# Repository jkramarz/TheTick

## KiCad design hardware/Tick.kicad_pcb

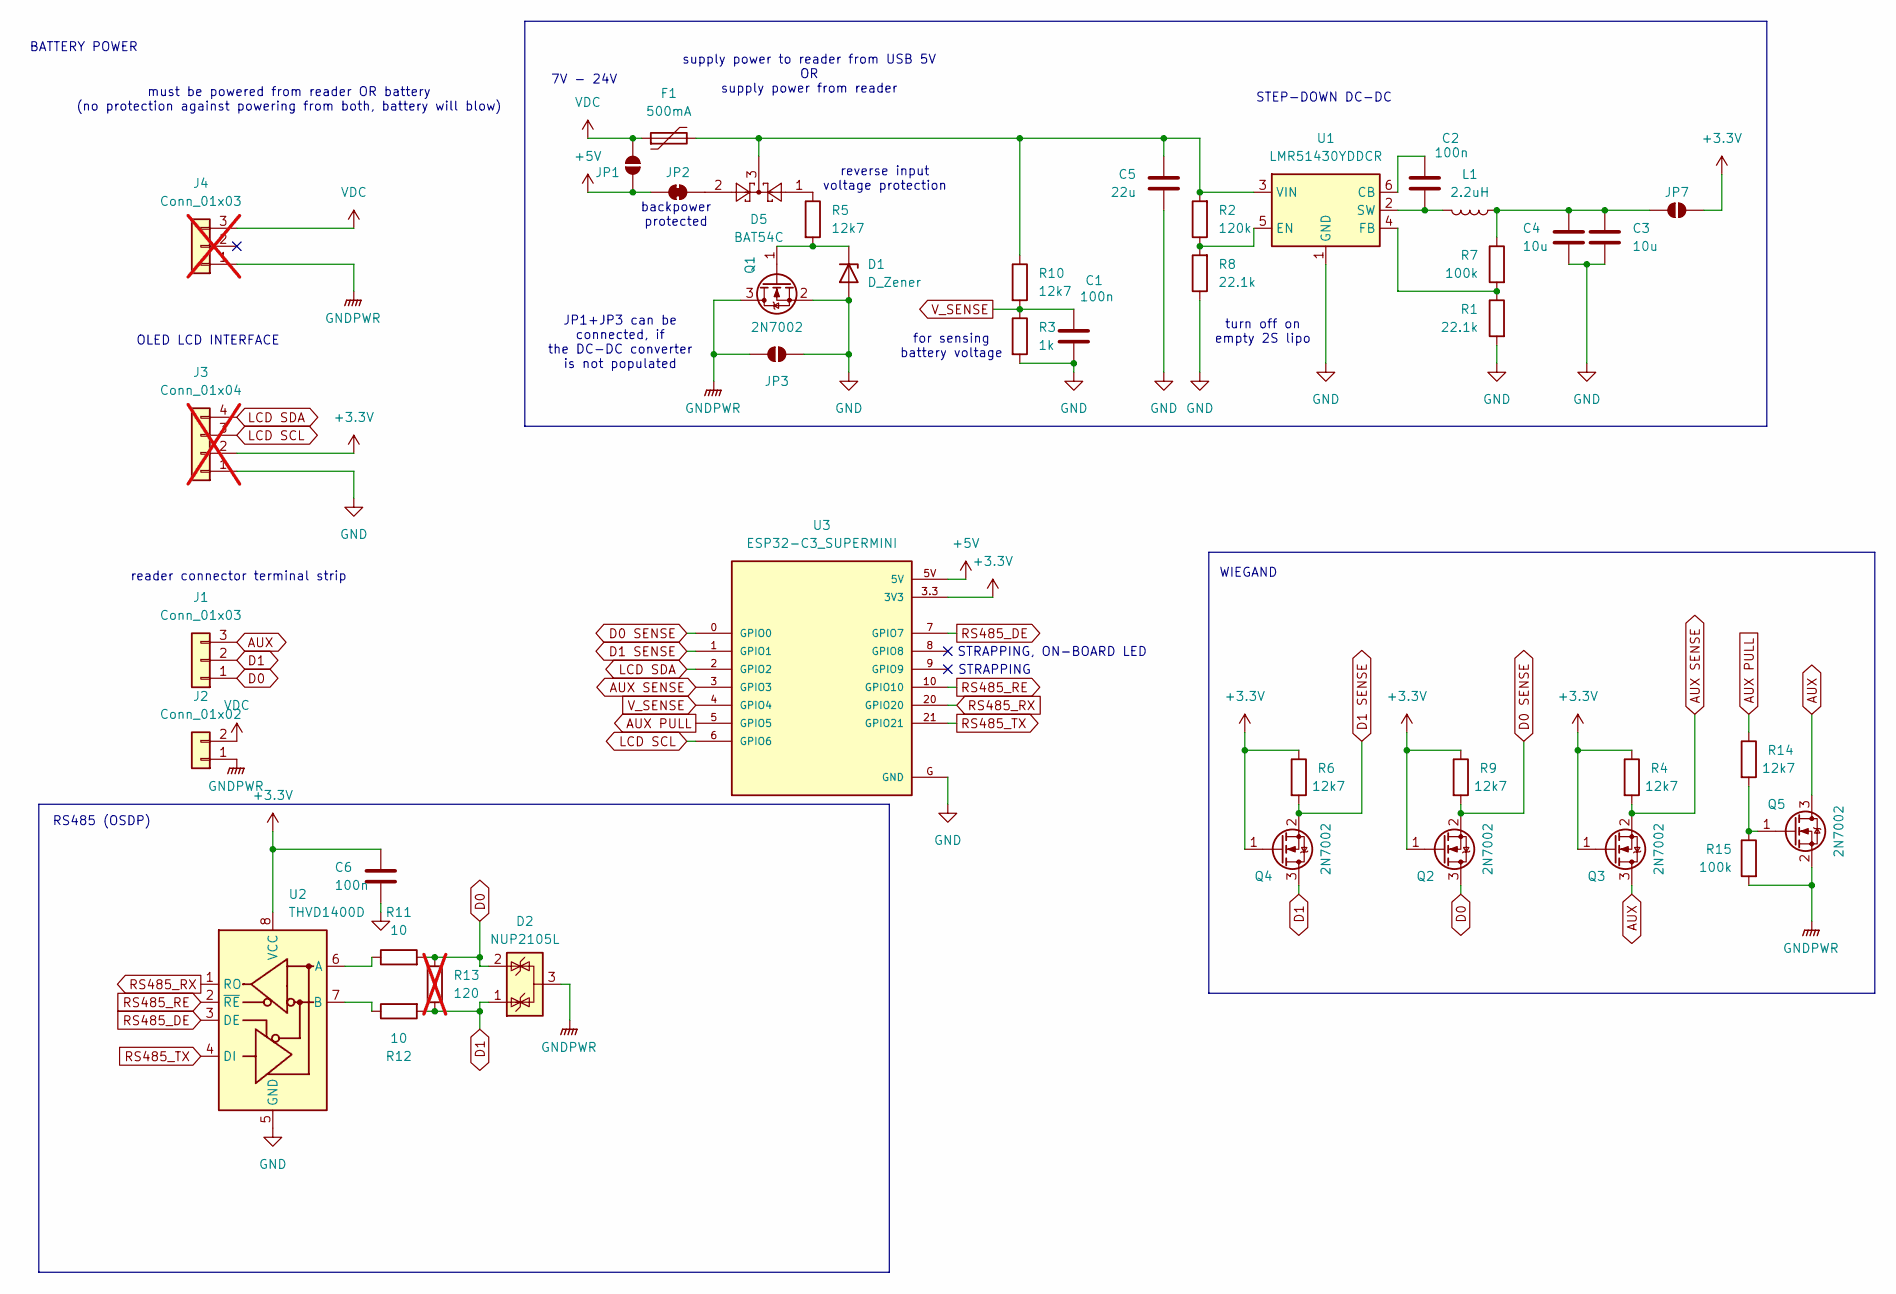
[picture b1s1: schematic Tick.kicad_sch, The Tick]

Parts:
C1, C2, C6: 100n; C_0805_2012Metric_Pad1.18x1.45mm_HandSolder
C3, C4: 10u; C_0805_2012Metric_Pad1.18x1.45mm_HandSolder
C5: 22u; C_1210_3225Metric_Pad1.33x2.70mm_HandSolder
D1: D_Zener; D_MiniMELF
D2: NUP2105L; SOT-23
D5: BAT54C; SOT-23
F1: 500mA; Fuse_1210_3225Metric_Pad1.42x2.65mm_HandSolder
J1: Conn_01x03; KYOCERA 009176003022006 PTH
J2: Conn_01x02; KYOCERA 009176002022006 PTH
J3: Conn_01x04; PinSocket_1x04_P2.54mm_Vertical; not fitted
J4: Conn_01x03; PinSocket_1x03_P2.54mm_Vertical; not fitted
JP1, JP2, JP3, JP7: SolderJumper_2_Open; SolderJumper-2_P1.3mm_Open_TrianglePad1.0x1.5mm
L1: 2.2uH; L_Changjiang_FXL0420
Q1, Q2, Q3, Q4, Q5: 2N7002; SOT-23
R1, R8: 22.1k; R_0603_1608Metric_Pad0.98x0.95mm_HandSolder
R2: 120k; R_0603_1608Metric_Pad0.98x0.95mm_HandSolder
R3: 1k; R_0603_1608Metric_Pad0.98x0.95mm_HandSolder
R4, R5, R6, R9, R10, R14: 12k7; R_0603_1608Metric_Pad0.98x0.95mm_HandSolder
R7, R15: 100k; R_0603_1608Metric_Pad0.98x0.95mm_HandSolder
R11, R12: 10; R_0603_1608Metric_Pad0.98x0.95mm_HandSolder
R13: 120; R_0603_1608Metric_Pad0.98x0.95mm_HandSolder; not fitted
U1: LMR51430YDDCR; SOT-23-6
U2: THVD1400D; SOIC-8_3.9x4.9mm_P1.27mm
U3: ESP32-C3_SUPERMINI; MODULE_ESP32-C3_SUPERMINI_SMD

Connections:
+3.3V: C6.1, J3.2, JP7.2 (B), Q2.1 (G), Q3.1 (G), Q4.1 (G), R4.1, R6.1, R9.1, U2.8 (VCC), U3.3.3 (3V3)
+5V: JP1.2 (B), JP2.1 (A), U3.5V
AUX: J1.3, Q3.3 (D), Q5.3 (D)
AUX PULL: R14.1, U3.5 (GPIO5)
AUX SENSE: Q3.2 (S), R4.2, U3.3 (GPIO3)
D0: D2.2 (K), J1.1, Q2.3 (D), R11.2, R13.2
D0 SENSE: Q2.2 (S), R9.2, U3.0 (GPIO0)
D1: D2.1 (K), J1.2, Q4.3 (D), R12.2, R13.1
D1 SENSE: Q4.2 (S), R6.2, U3.1 (GPIO1)
GND: C1.2, C3.2, C4.2, C5.2, C6.2, D1.2 (A), J3.1, JP3.1 (A), Q1.2 (S), R1.2, R3.2, R8.1, U1.1 (GND), U2.5 (GND), U3.G (GND)
GNDPWR: D2.3 (A), J2.1, J4.1, JP3.2 (B), Q1.3 (D), Q5.2 (S), R15.2
LCD SCL: J3.3, U3.6 (GPIO6)
LCD SDA: J3.4, U3.2 (GPIO2)
unnamed: D1.1 (K), Q1.1 (G), R5.2
unnamed: D5.1, R5.1
unnamed: D5.2, JP2.2 (B)
unnamed: C3.1, C4.1, JP7.1 (A), L1.1, R7.1
unnamed: Q5.1 (G), R14.2, R15.1
unnamed: C2.1, U1.6 (CB)
unnamed: R2.1, R8.2, U1.5 (EN)
unnamed: R1.1, R7.2, U1.4 (FB)
unnamed: C2.2, L1.2, U1.2 (SW)
unnamed: C5.1, D5.3, F1.2, R2.2, R10.1, U1.3 (VIN)
unnamed: R11.1, U2.6 (A)
unnamed: R12.1, U2.7 (B)
RS485_DE: U2.3 (DE), U3.7 (GPIO7)
RS485_RE: U2.2 (~RE), U3.10 (GPIO10)
RS485_RX: U2.1 (RO), U3.20 (GPIO20)
RS485_TX: U2.4 (DI), U3.21 (GPIO21)
VDC: F1.1, J2.2, J4.3, JP1.1 (A)
V_SENSE: C1.1, R3.1, R10.2, U3.4 (GPIO4)

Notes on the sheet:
supply power to reader from USB 5V OR supply power from reader
STEP-DOWN DC-DC
JP1+JP3 can be connected, if the DC-DC converter is not populated
OLED LCD INTERFACE
reader connector terminal strip
reverse input voltage protection
must be powered from reader OR battery (no protection against powering from both, battery will blow)
7V - 24V
BATTERY POWER
backpower protected
WIEGAND
turn off on empty 2S lipo
STRAPPING, ON-BOARD LED
for sensing battery voltage
STRAPPING
RS485 (OSDP)

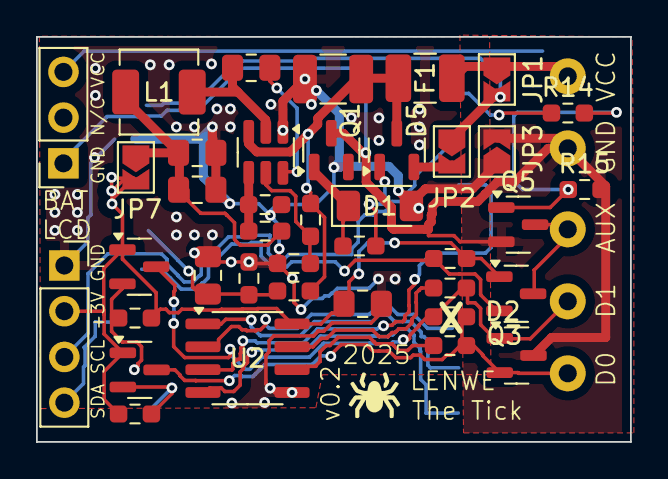
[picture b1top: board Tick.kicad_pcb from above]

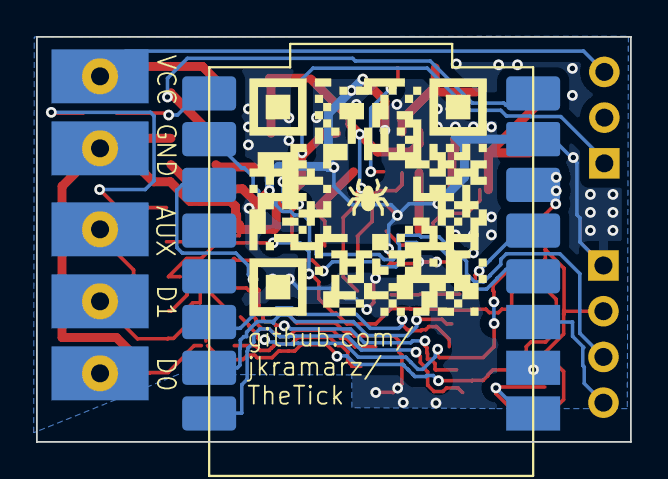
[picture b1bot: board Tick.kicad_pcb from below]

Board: 2 copper layers, 33.0 x 22.5 mm, 42 parts (3 on the bottom side), 31 nets.

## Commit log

2025-03-24 remove google fonts
    When Tick is used in offline scenario, downloading google fonts fails
    which delays UI loading.
2025-03-24 Fix clear HTTP handler, fixes #1
2025-04-05 added strong current sink on AUX

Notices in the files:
hardware/Tick.kicad_pcb:
Copyright (C) 2024, 2025 Jakub \"lenwe\" Kramarz
CERN Open Hardware Licence Version 2 - Strongly Reciprocal
